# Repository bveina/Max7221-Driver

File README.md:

# Max7221-Driver
PCB and atmel code to drive two 4-digit 7-segment displays

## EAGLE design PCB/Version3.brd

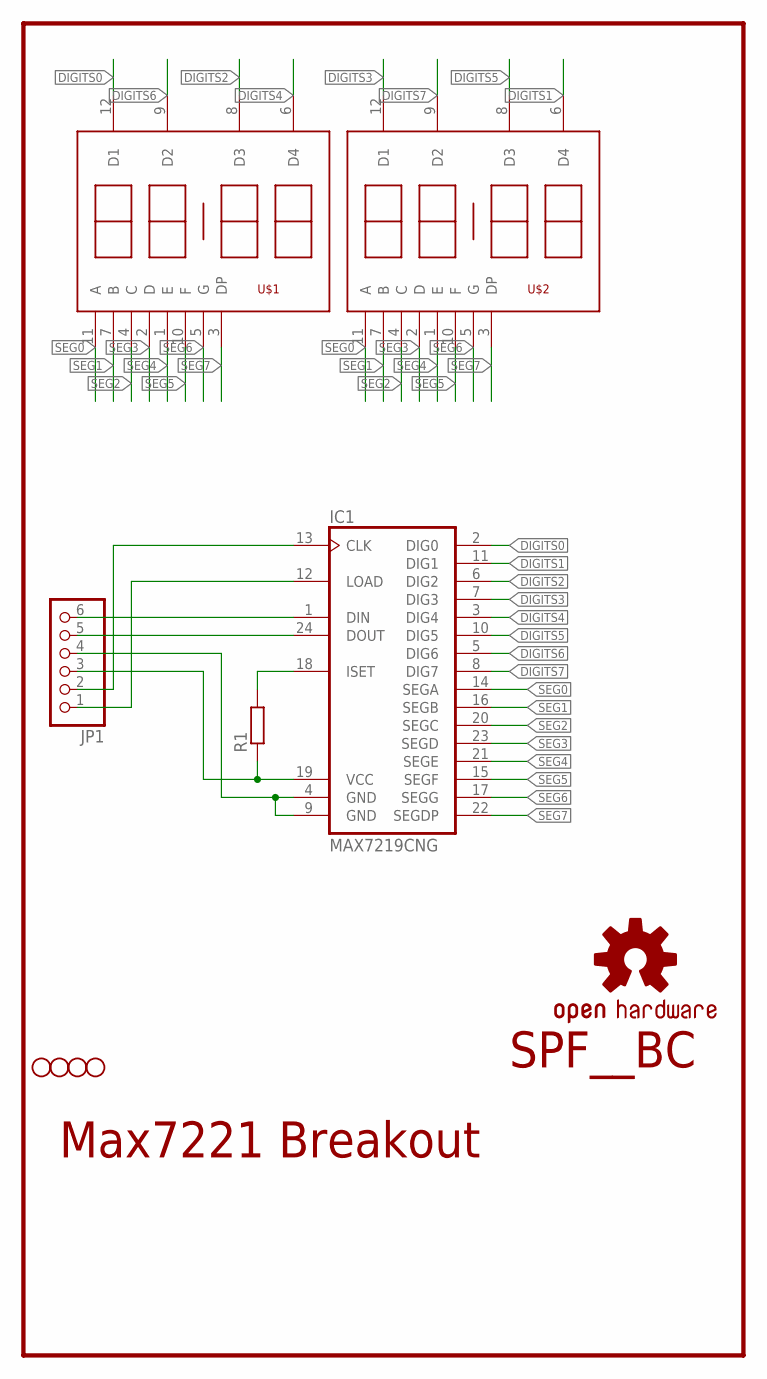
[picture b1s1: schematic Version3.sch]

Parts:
H1, H2, H3, H4: STAND-OFF
IC1: MAX7219CNG; DIL24-3
JP1: PINHD-1X6CLEAN; 1X06-CLEAN
LOGO1: OSHW-LOGOL; OSHW-LOGO-L
R1: R-EU_0207/10; 0207/10
U$1, U$2: 4DIG_7SEG_CATHODE; 4DIG_7SEG_CLOCK

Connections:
DIGITS0: IC1.2 (DIG0), U$1.12 (D1)
DIGITS1: IC1.11 (DIG1), U$2.6 (D4)
DIGITS2: IC1.6 (DIG2), U$1.8 (D3)
DIGITS3: IC1.7 (DIG3), U$2.12 (D1)
DIGITS4: IC1.3 (DIG4), U$1.6 (D4)
DIGITS5: IC1.10 (DIG5), U$2.8 (D3)
DIGITS6: IC1.5 (DIG6), U$1.9 (D2)
DIGITS7: IC1.8 (DIG7), U$2.9 (D2)
DIN: IC1.1 (DIN), JP1.6
DOUT: IC1.24 (DOUT), JP1.5
GND: IC1.4 (GND), IC1.9 (GND), JP1.4
ISET: IC1.18 (ISET), R1.2
LOAD: IC1.12 (LOAD), JP1.1
SCLK: IC1.13 (CLK), JP1.2
SEG0: IC1.14 (SEGA), U$1.11 (A), U$2.11 (A)
SEG1: IC1.16 (SEGB), U$1.7 (B), U$2.7 (B)
SEG2: IC1.20 (SEGC), U$1.4 (C), U$2.4 (C)
SEG3: IC1.23 (SEGD), U$1.2 (D), U$2.2 (D)
SEG4: IC1.21 (SEGE), U$1.1 (E), U$2.1 (E)
SEG5: IC1.15 (SEGF), U$1.10 (F), U$2.10 (F)
SEG6: IC1.17 (SEGG), U$1.5 (G), U$2.5 (G)
SEG7: IC1.22 (SEGDP), U$1.3 (DP), U$2.3 (DP)
VCC: IC1.19 (VCC), JP1.3, R1.1

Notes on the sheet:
Max7221 Breakout
SPF__BC

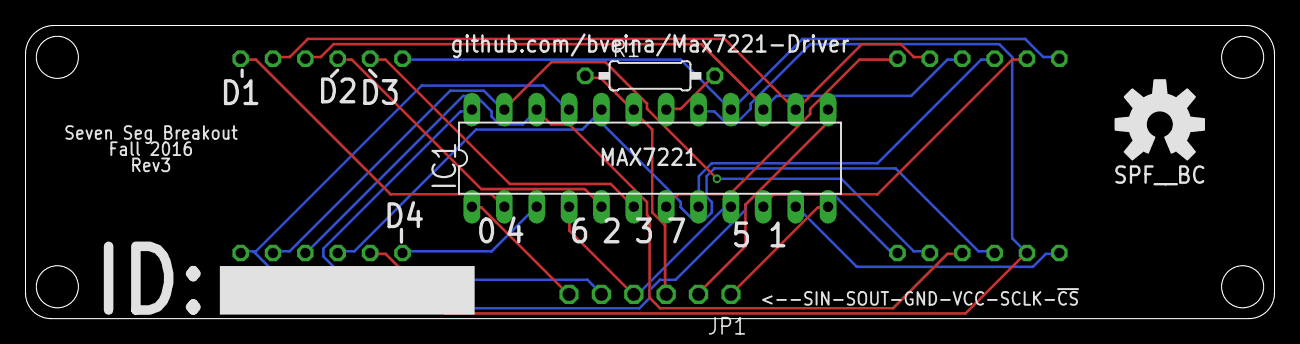
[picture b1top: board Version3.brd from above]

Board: 2 copper layers, 98.0 x 23.0 mm, 10 parts (0 on the bottom side), 23 nets.

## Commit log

2016-09-20 initial file dump
2016-09-30 made code lib arduino compliant, added verification code
    put the INO file inside a folder of the same name,
    added the hex font and test code

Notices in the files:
parts and their libraries:
SparkFun-Aesthetics: Licensing: Creative Commons ShareAlike 4.0 International - https://creativecommons.org/licenses/by-sa/4.0
